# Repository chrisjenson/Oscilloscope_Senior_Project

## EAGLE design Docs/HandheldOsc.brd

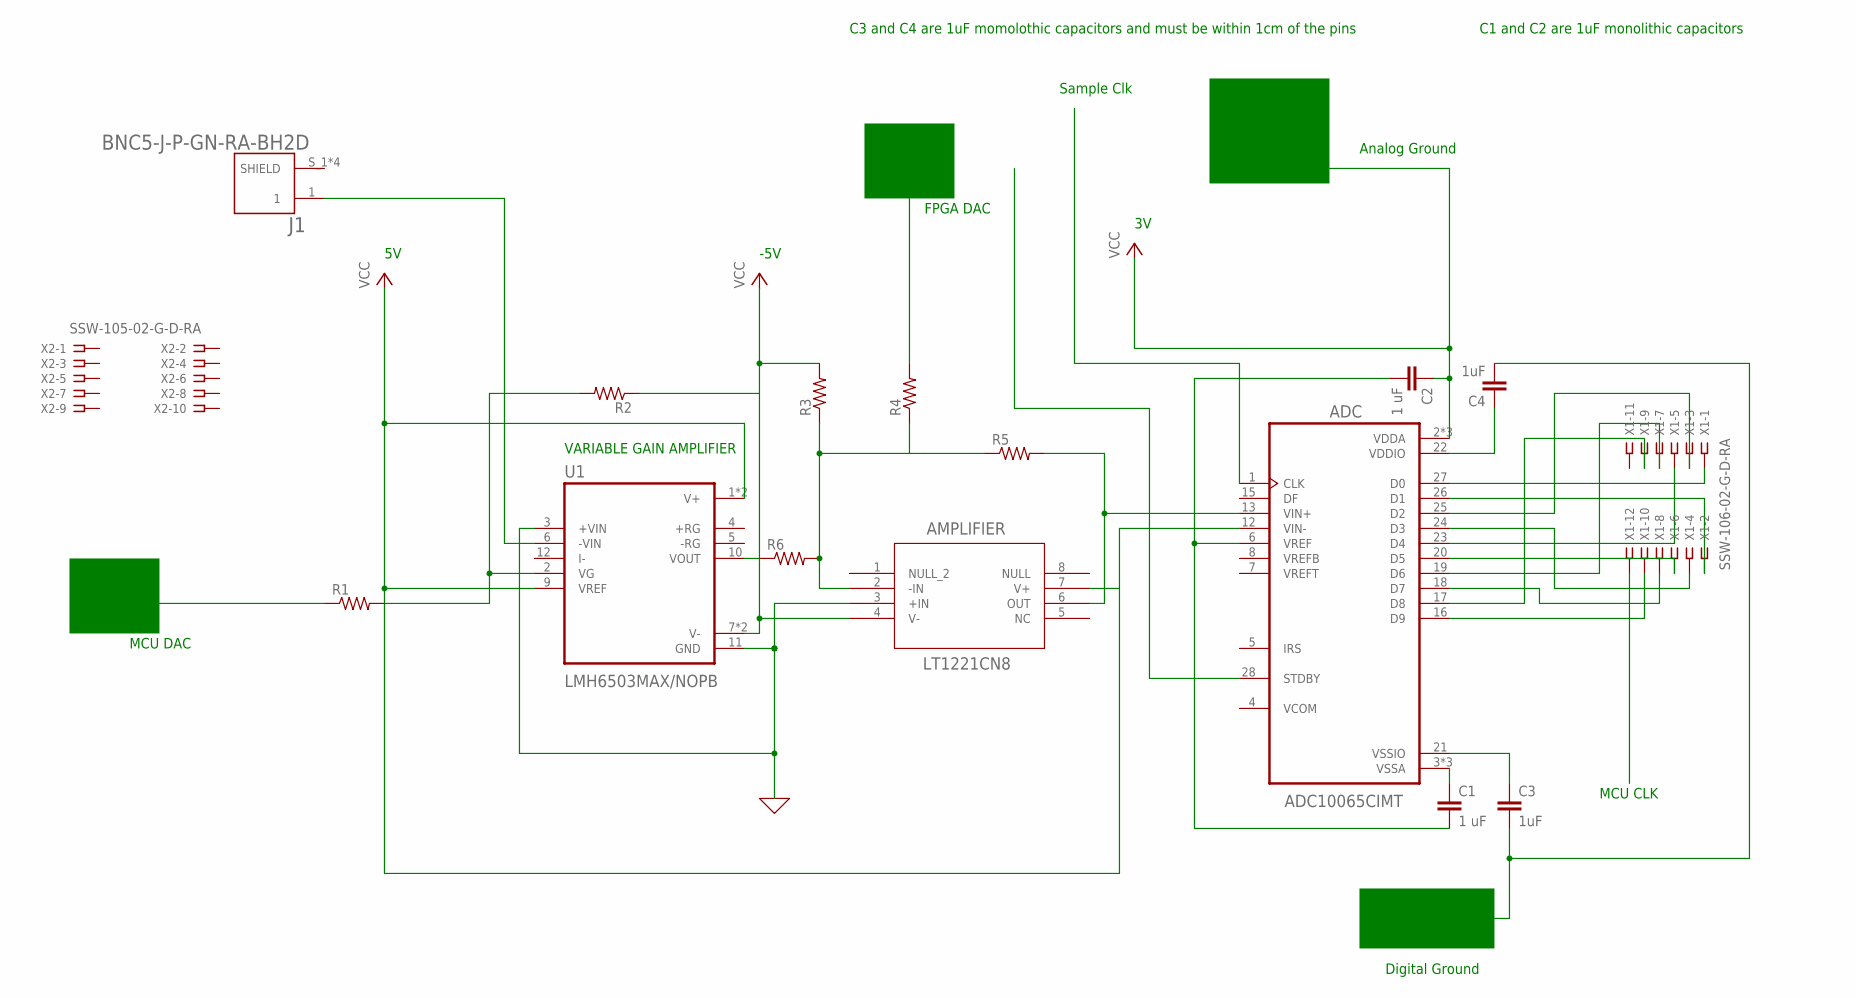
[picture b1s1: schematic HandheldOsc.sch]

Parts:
ADC: ADC10065CIMT; SOP65P640X120-28N
AMPLIFIER: LT1221CN8; PDIP-8_N
C1, C2: 1 uF; C2.5-3
C3, C4: 1uF; C2.5-3
J1: BNC5-J-P-GN-RA-BH2D; SAMTEC_BNC5-J-P-GN-RA-BH2D
R1, R2, R3, R4, R5, R6: R-US_0207/12; 0207/12
U1: LMH6503MAX/NOPB; SOIC127P600X175-14N
X1: SSW-106-02-G-D-RA
X2: SSW-105-02-G-D-RA

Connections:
0: AMPLIFIER.3 (+IN), U1.3 (+VIN), U1.11 (GND)
unnamed: R6.1, U1.10 (VOUT)
unnamed: AMPLIFIER.2 (-IN), R3.1, R4.1, R5.1, R6.2
unnamed: ADC.13 (VIN+), AMPLIFIER.6 (OUT), R5.2
unnamed: J1.1, U1.6 (-VIN)
unnamed: ADC.27 (D0), X1.1
unnamed: R1.2, R2.2, U1.2 (VG)
unnamed: ADC.26 (D1), X1.2
unnamed: ADC.25 (D2), X1.3
unnamed: ADC.24 (D3), X1.4
unnamed: ADC.23 (D4), X1.5
unnamed: ADC.20 (D5), X1.6
unnamed: ADC.19 (D6), X1.7
unnamed: ADC.18 (D7), X1.8
unnamed: ADC.17 (D8), X1.9
unnamed: ADC.16 (D9), X1.10
unnamed: ADC.6 (VREF), C1.2, C2.2
unnamed: ADC.3 (VSSA), ADC.11 (VSSA), ADC.14 (VSSA), C1.1
unnamed: ADC.22 (VDDIO), C4.1
unnamed: C3.2, C4.2
unnamed: ADC.21 (VSSIO), C3.1
VCC: ADC.2 (VDDA), ADC.9 (VDDA), ADC.10 (VDDA), ADC.12 (VIN-), AMPLIFIER.4 (V-), AMPLIFIER.7 (V+), C2.1, R2.1, R3.2, U1.1 (V+), U1.7 (V-), U1.8 (V-), U1.9 (VREF), U1.14 (V+)

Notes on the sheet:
VARIABLE GAIN AMPLIFIER
-5V
FPGA DAC
MCU DAC
MCU CLK
Sample Clk
C1 and C2 are 1uF monolithic capacitors
Analog Ground
Digital Ground
C3 and C4 are 1uF momolothic capacitors and must be within 1cm of the pins

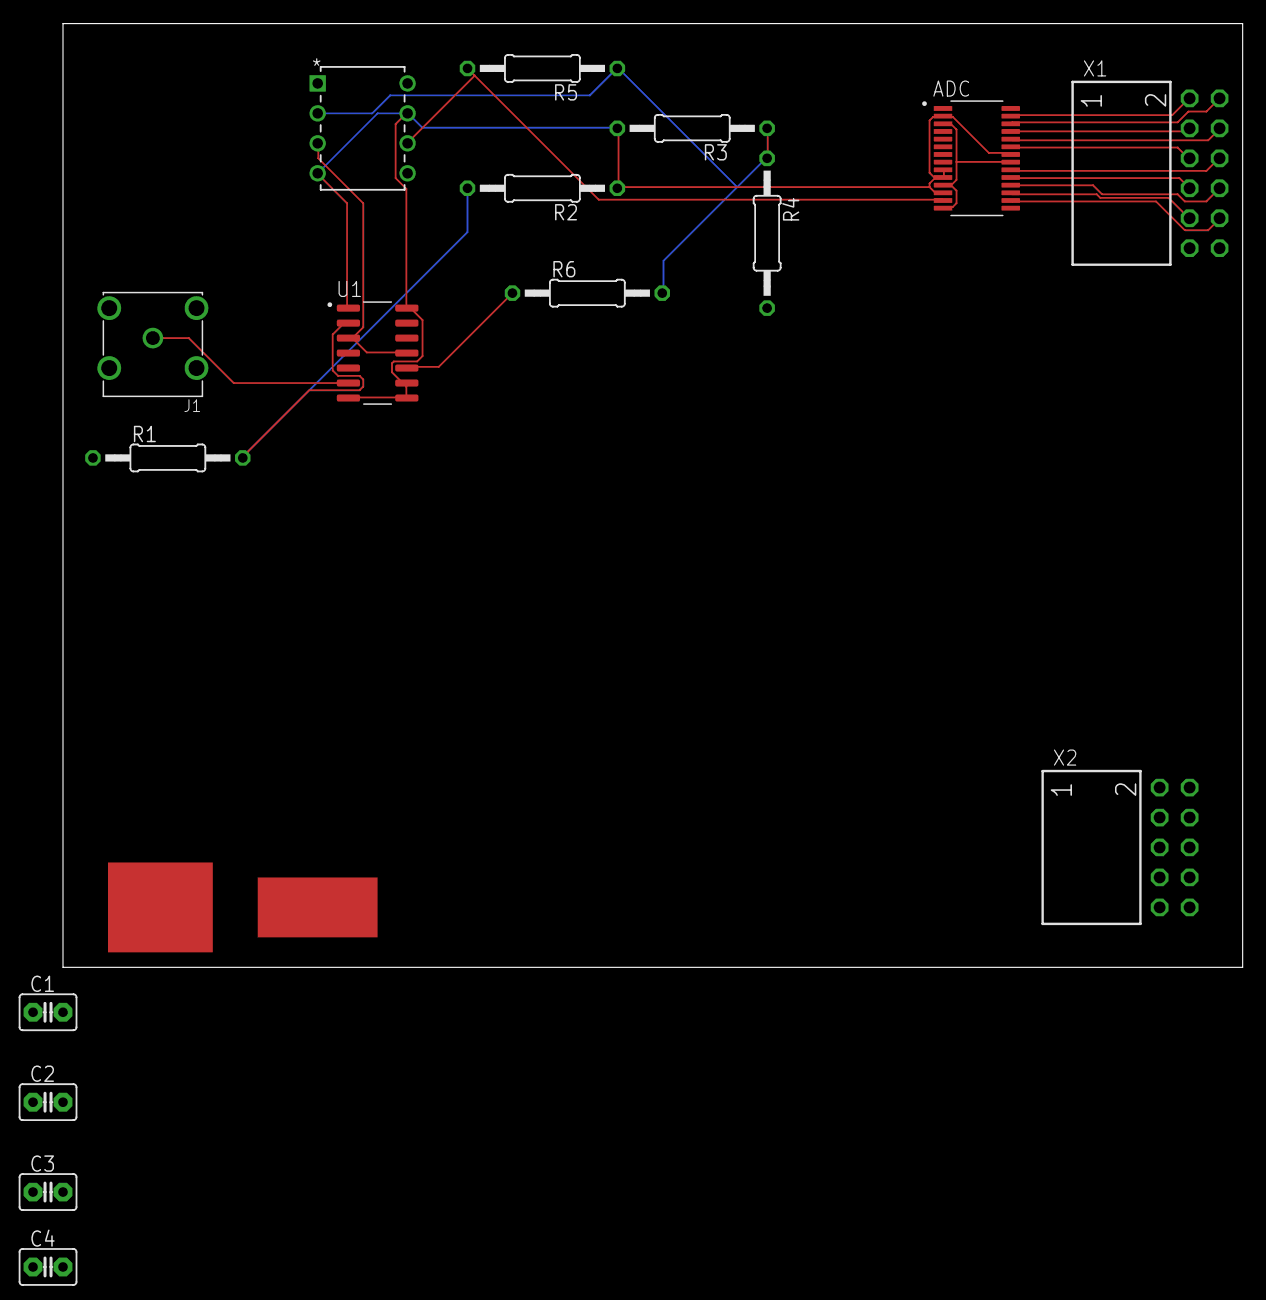
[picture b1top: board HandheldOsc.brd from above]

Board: 2 copper layers, 100.0 x 80.0 mm, 16 parts (0 on the bottom side), 22 nets.

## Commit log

2020-09-20 added code
2020-10-04 Adding additional files
2020-10-11 Interfaces Designed
2020-10-14 The MCU PSOC project
2020-10-20 New changes
2020-10-26 Add files via upload
    DAB Schematic V1 (incomplete)
2020-10-26 DAB Schematic and Board
    DAB Schematic and Board V.1 (Incomplete)
2020-10-26 DAB Schematic
    DAB Schematic V.1 (Incomplete)
2020-10-26 DAB Board
    DAB Board V.1 (Incomplete)
2020-10-26 SPI testing and Updated interfaces
2020-10-30 SPI Test Read done
2020-11-01 updates to SPI
2020-11-02 SPI Code v1
2020-11-07 SPI Ram read updates
2020-11-08 FIFO added
2020-11-15 Beginning SPI Version 3
2020-11-16 DAB Schematic V1
    DAB Schematic V1 (ordered on JLCPCB)
2020-11-16 DAB Schematic V1.1
    DAB Schematic V1.1 (order on JLCPCB)
2020-11-16 DAB Board V1.1
    DAB Board V1.1 (order on JLCPCB)
2020-11-18 SPI Pre code review- write and read functional but not great
2020-11-18 Updating PSoC
2020-11-18 Create LICENSE
2020-11-18 Code for review
2020-11-20 Version 2 of DAB Interface in progress
2020-11-22 Pre-test with Chris
2020-11-23 Switching Data concatenation to front end from back end
2020-11-23 Ready for full system integration V0.5
2020-11-23 MCU SPI work
2020-11-23 MCU display work
2020-11-24 In person lab update, combining front end and backend code next
2020-11-24 Debugging in progress, V0.5
2020-11-25 Debugging in progress
2020-11-25 Small change to debugging output
2020-11-25 Git missed a few files
2020-11-25 Improving and debugging ram read code
2020-11-25 updating spi implementation for unit testing
2020-11-28 Reading and writing!
2020-11-28 MCU sliders working
2020-11-29 Debugging continuing
2020-11-29 Repaired Reg Write
2020-11-29 Updates to naming for report
2020-11-29 functioning display
2020-11-30 new header file to fix overwriting
2020-12-01 Newest SPI code
2020-12-04 Semester 1 final version
2021-02-12 psoc updates
2021-02-13 Testbench Improvements
2021-02-14 Begining Trigger logic
2021-02-19 Debugging inprovements and Triggering
2021-02-21 MCU update
2021-02-25 Much improved SPI
2021-02-27 tested SPI code
2021-02-28 SPI cleanup
2021-02-28 data splitting
2021-02-28 Additional resets and debug improvements
2021-03-03 Fix Attmept
2021-03-05 MCU offset implemented
2021-03-11 Trigger functionality
2021-03-12 Trigger implemented
2021-03-12 Horizontal score, trigger edge, and some scalling
2021-03-12 MCU code to voltage
2021-03-18 Trigger in progress, interface functional
2021-03-18 Triggering in good shape... Needs testing
2021-03-18 Scaling looks promising, offset may be broken
2021-03-18 Offset fixed
2021-03-18 signal generation project for PSoC
2021-03-18 Offset, both scales, & horizontal scrolling working
2021-03-21 Making a new branch Because i am not suree this was good
2021-03-24 MCU trigger added to display and other UI changes
2021-03-24 comments
2021-03-26 MCU UI Rearranging in progress
2021-03-26 offset scaling fixed
2021-03-31 MCU Trigger early SPI Code
2021-03-31 code transfer
2021-04-03 Trigger test time!
2021-04-07 Bitstream Failing
2021-04-08 Trigger Test
2021-04-10 6 hours of bug fixing and Testbench improvements... Also reducing filesizes
2021-04-12 MCU SPI fixes
2021-04-14 MCU Slave Select changes
2021-04-16 MCU sending signed trigger
2021-04-16 changed MCU SPI if structure to a switch statement
2021-04-16 Trigger good!
2021-04-16 MCU code quality of life changes
2021-04-22 MCU repeated single sweep to test
2021-04-22 MCU updates
2021-04-23 adding offset to the displayed trigger
2021-04-23 sine in sine out
2021-04-23 switch between single and normal triggering
2021-04-23 sine in sine out normal trigger
2021-04-23 MCU working
2021-04-30 SPI data rate increased
2021-04-30 MCU clock set
2021-04-30 MCU Final Farewell
2021-05-06 Final Version: Submitted
